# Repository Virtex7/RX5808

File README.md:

# RX5808
FPV Empfänger mit OSD auf OLED, Diversitysupport und vielem mehr.

Software basierend auf dem Projekt von Marko Hoepken
https://code.google.com/p/rx5808-pro/wiki/Overview

sowie inzwischen dem Code des rx5808-pro-diversity von hier:
https://github.com/sheaivey/rx5808-pro-diversity

Es wurden diese Platinen entworfen, um einen vielseitigen FPV-Empfänger bauen zu können

Diese Doku beschränkt sich auf die Hardware, weil die Software schon bei *sheaivey* sehr schön dokumentiert ist.

## Hinweise zur Hardware

Der Hauptgrund für den Bau dieses Moduls ist, dass ich gern ein Modul für die lokale FPV- und Modellbaugruppe designen wollte, das nicht nur die üblichen Funktionen wie freie Kanalwahl, Bandscanner für die Kanalbelegung und übersichtliche Anzeige der Daten hat, sondern auch Diversität unterstützt und allgemein ein schöneres Design hat, als die üblichen Aufbauten. Auch der Schaltwandler direkt auf dem Board hat für eine Bodenstation oder sogar Verwendung direkt an der VR-Brille klare Vorteile.

Dazu kommt, dass ich noch zusätzlich einen HF-Vorverstärker und einen Kopfhöreranschluss verbauen wollte, damit dem Piloten mehr Optionen offen bleiben und das Modul einen Mehrwert gegenüber anderen käuflichen Modulen hat.

Der HF-Verstärker ist auf das 5,8GHz-Band ausgelegt und hat ein Sperrfilter für Signale im 2,4GHz-Band, was im Modellbau heutzutage die Fernsteuerung darstellt. Diese Signale können sonst den Videoempfänger stören und zu Bildstörungen oder sogar dem Totalausfall des Bildes führen, was für die FPV-Piloten fatal ist.

Achtung: HF-Verstärker und Tonausgabe stehen nur bei Verwendung des optionalen Diversity-Moduls zur Verfügung! Es wird auch klar empfohlen, an das Diversity-Erweiterungsmodul keine Richtantennen anzuschließen, wenn der Copter mit einem Funkmodul mit über 25mW Ausgangsleistung und/oder einer Richtantenne ausgestattet ist. Solche Antennen gehören erst mal das Haupt-Empfangsmodul, weil sonst die Gefahr besteht, den Videoempfänger zu überlasten und damit das Videobild zu stören.

Das Diversity-Modul wird automatisch erkannt und dann auch im Menü angezeigt. Es muss keine Änderung an der Software vorgenommen werden. Im Diversity-Modus zeigt eine grüne LED an, welches Modul gerade das Videosignal an den Ausgang liefert. Die Umschaltung zwischen den Empfängern erfolgt für das Videobild unsichtbar.

Schließlich lässt sich noch ein kompatibler Videosender durch eine IR-Schnittstelle auf den gewünschten Kanal einstellen, die dazu nötige IR-Sendediode D5 liegt an einer Platinenecke direkt neben der SMA-Buchse.

## Aufbau
Bestellnummern werden nur bei Bauteilen angegeben, die nicht als "Standardbauteil, also wie ein normaler Kondensator oder Widerstand aus der E12-Reihe, bezeichnet werden können. Leider reicht es nicht aus, ausschließlich bei Digikey zu bestellen, da hier einzelne Teile nicht verfügbar sind. Es gibt in Deutschland keinen Distributor, der alle benötigten Teile liefern kann.

### Bill of Material
| Anzahl | Bauteilname | Gehäuseform | Referenz(en) auf der Platine | Digikeynummer |
| ------ | ----------- | ----------- | ---------------------------- | ------------- |
|

### Platinenlayouts und Löten
Die Platine sind mit KiCAD, einer Version >> 4.0 erstellt und müssen auch damit exportiert werden. Generelle Tips dazu kann ich nicht geben, da es viel zu ausführlich werden würde. Ich empfehle jedoch nicht, für einen Nachbau die Daten direkt zu verwenden, die im Gerber-Verzeichnis sind, sondern stets selbst Fertigungsdaten zu exportieren.

Durch die vielen SMD-Bauteile und vor allem das HF-Filter auf der Diversityplatine bietet sich Reflowlöten klar an. Die Lötpaste kann mittels Dispenser oder auch durch Rakeln aufgebracht werden, wobei ein besonderes Augenmerk auf den kleinen Bauteilen **TPS62160** und **LP38798** gelegt werden sollte. Diese haben ein recht feines Pinraster und kleine Pads, was leicht dazu führen kann, dass die falsche Menge Lötpaste aufgetragen wird.

Von der Reihenfolge her sollte man zuerst die kleinen, meist passiven, Bauelemente auflöten und dann mit den ICs und ggf. Steckern weitermachen. So stehen sich die Bauteile nicht beim Bestücken gegenseitig im Weg herum. Achtung! vor dem Programmieren des Bootloaders **DARF** das OLED noch **NICHT** eingelötet sein, weil man sonst nicht mehr an den Atmel herankäme.

### Test
Bevor das Modul programmiert werden kann, muss es getestet werden. Es geht hier ausschließlich darum, ob der Schaltwandler die richtige Ausgangsspannung liefert. Achtung: nur wenn R21 gesetzt ist, kann der Schaltwandler korrekt arbeiten. Ansonsten gibt er eine leicht zu hohe Spannung aus, weil die Ausgangslast zu gering ist.

Achtung bei der Montage des Kabels zwischen Hauptmodul und Diversityplatine! Die Verpolschutznasen der Micromatchstecker brechen leicht ab und die Diversityplatine ist nicht explizit verpolgeschützt. Daher vor Einschalten der Stromversorgung auf jeden Fall auf korrekte Verkabelung kontrollieren. Beim Verpolen wird zwar die 5V-Versorgung des Moduls auf einen absichtlich nicht verwendeten Pin gelegt, aber durch die Steuersignale könnte dennoch ein Latch-Up-Effekt auftreten.

Die Eingangsspannung wird an den JST-XH-Stecker mit vier Pins angeschlossen, so lange keine Betriebsspannung in den Videoausgang eingespeist wird, ist das Modul verpol- und Überspannungsgeschützt. Sinnvollerweise sollte die Stromversorgung an die beiden oberen Pins des Steckers (Modul liegt so auf dem Tisch, dass der Versorgungsstecker *P1* links liegt) Pin 1 des Steckers ist Power-Masse und Pin 2 Stromversorgung. Für den Test wird hier eine Spannung von 6V eingespeist, weil diese den Mikrocontroller nicht schädigt, wenn der Schaltwandler noch nicht funktioniert, aber eigendlich schon auf 5,0V heruntergeregelt werden sollte. Die Ausgangsspannung kann über den Kondensator C10 leicht gemessen werden; wenn sie passt, also im Breich 4,9 bis 5,1V liegt und sich auch bei Variation der Eingangsspannung nicht ändert, darf die Eingangsspannung auf bis zu 15V angehoben werden. Die Stromaufnahme des Moduls muss hier ohne Empfängermodul etwa bei 10mA liegen. Deutlich höhere Stromaufnahme deutet fast immer auf einen Lötfehler hin.

## Inbetriebnahme
Zuerst muss der Bootloader geflasht werden. Dazu ein ISP-Programmiergerät an den Atmel (ATMEGA328P) anschließen und die Arduino/Genduino-IDE starten. Als Board wird der *Arduino Nano* ausgewählt, der Prozessor ist ein *atmega328* Wenn der Programmiervorgang erfolgreich war, blinkt die eine grüne LED des Hauptboardes mit 1Hz Takt und zeigt so an, dass der Bootloader aufgespielt ist und die Fuses korrekt gesetzt sind.

Jetzt darf das OLED eingelötet werden. **Tipp:** es empfiehlt sich, das OLED mit einem kleinen Stückchen doppelseitigem Klebeband vorne auf den JST-PH-5-Stecker zu kleben, da es so fest ist und nach anlöten nicht mehr verrutschen kann.

### Programmieren der Software

Die Software aus dem Submodul *rx5808-pro-diversity* wird in der Arduino-IDE geöffnet. IDE-Version ab 1.6.6 habe ich getestet, es sollten aber auch frühere Versionen funktionieren. Näheres dazu findet man auch in der Doku beim Entwickler der Software.

**Tipp:** in der Datei *settings.h* lässt sich ein CallSign mit bis zu 10 Zeichen, also z.B. der Name des Piloten, einstellen. Es ist weitaus angenehmer, dieses in der Software am PC einzustellen, als es mit dem kleinen Navigation-Switch direkt am Modul einzugeben.

### Bedienung

Die genaue Bedienung des Geräts ist beim Entwickler der Software zu finden, so viel von mir dazu: Der Navigation-Switch lässt sich nach oben und unten kippen sowie eindrücken. Kippen erzeugt die Funktionen *hoch* und *runter*, Drücken ist die Funktion *Menü* oder im Menü dann *bestätigen*

Es empfiehlt sich, das Modul vor dem ersten richtigen Einsatz zu kalibrieren, der genaue Ablauf steht auch hier in der Softwaredoku.

## Abschließende Hinweise
Das Modul kann eingeschrumpft werden. Dabei bitte auf das OLED aufpassen, die Ecken des Displayglases brechen leicht ab und nehmen dann einen Teil des Folienleiters mit, was das Display zerstört. Ich empfehle, vor dem Einschrumpfen eine kleine Menge Klebstoff unter die Displayecken zu geben, damit diese mechanisch fest sind.
Der Programmierstecker an der unteren Kante des Moduls kann verschlossen werden, er wird für den Betrieb nicht benötigt.

Es ist auch möglich, statt des XH-Steckers für Strom und Videosignal ein Servokabel zu verwenden, auch wenn dies von mir klar nicht empfohlen wird, weil so keine Massetrennung zwischen Signal und Videosignal stattfindet und das Servokabel nicht ziegeschützt ist.
Die Belegung ist so gewählt, dass beim Servokabel Rot und Schwarz die Stromversorgung darstellt und die Signalader das Videosignal führt. Für Tests, oder wenn man gerade keinen XH-Stecker da hat, sicher eine gute Möglichkeit.

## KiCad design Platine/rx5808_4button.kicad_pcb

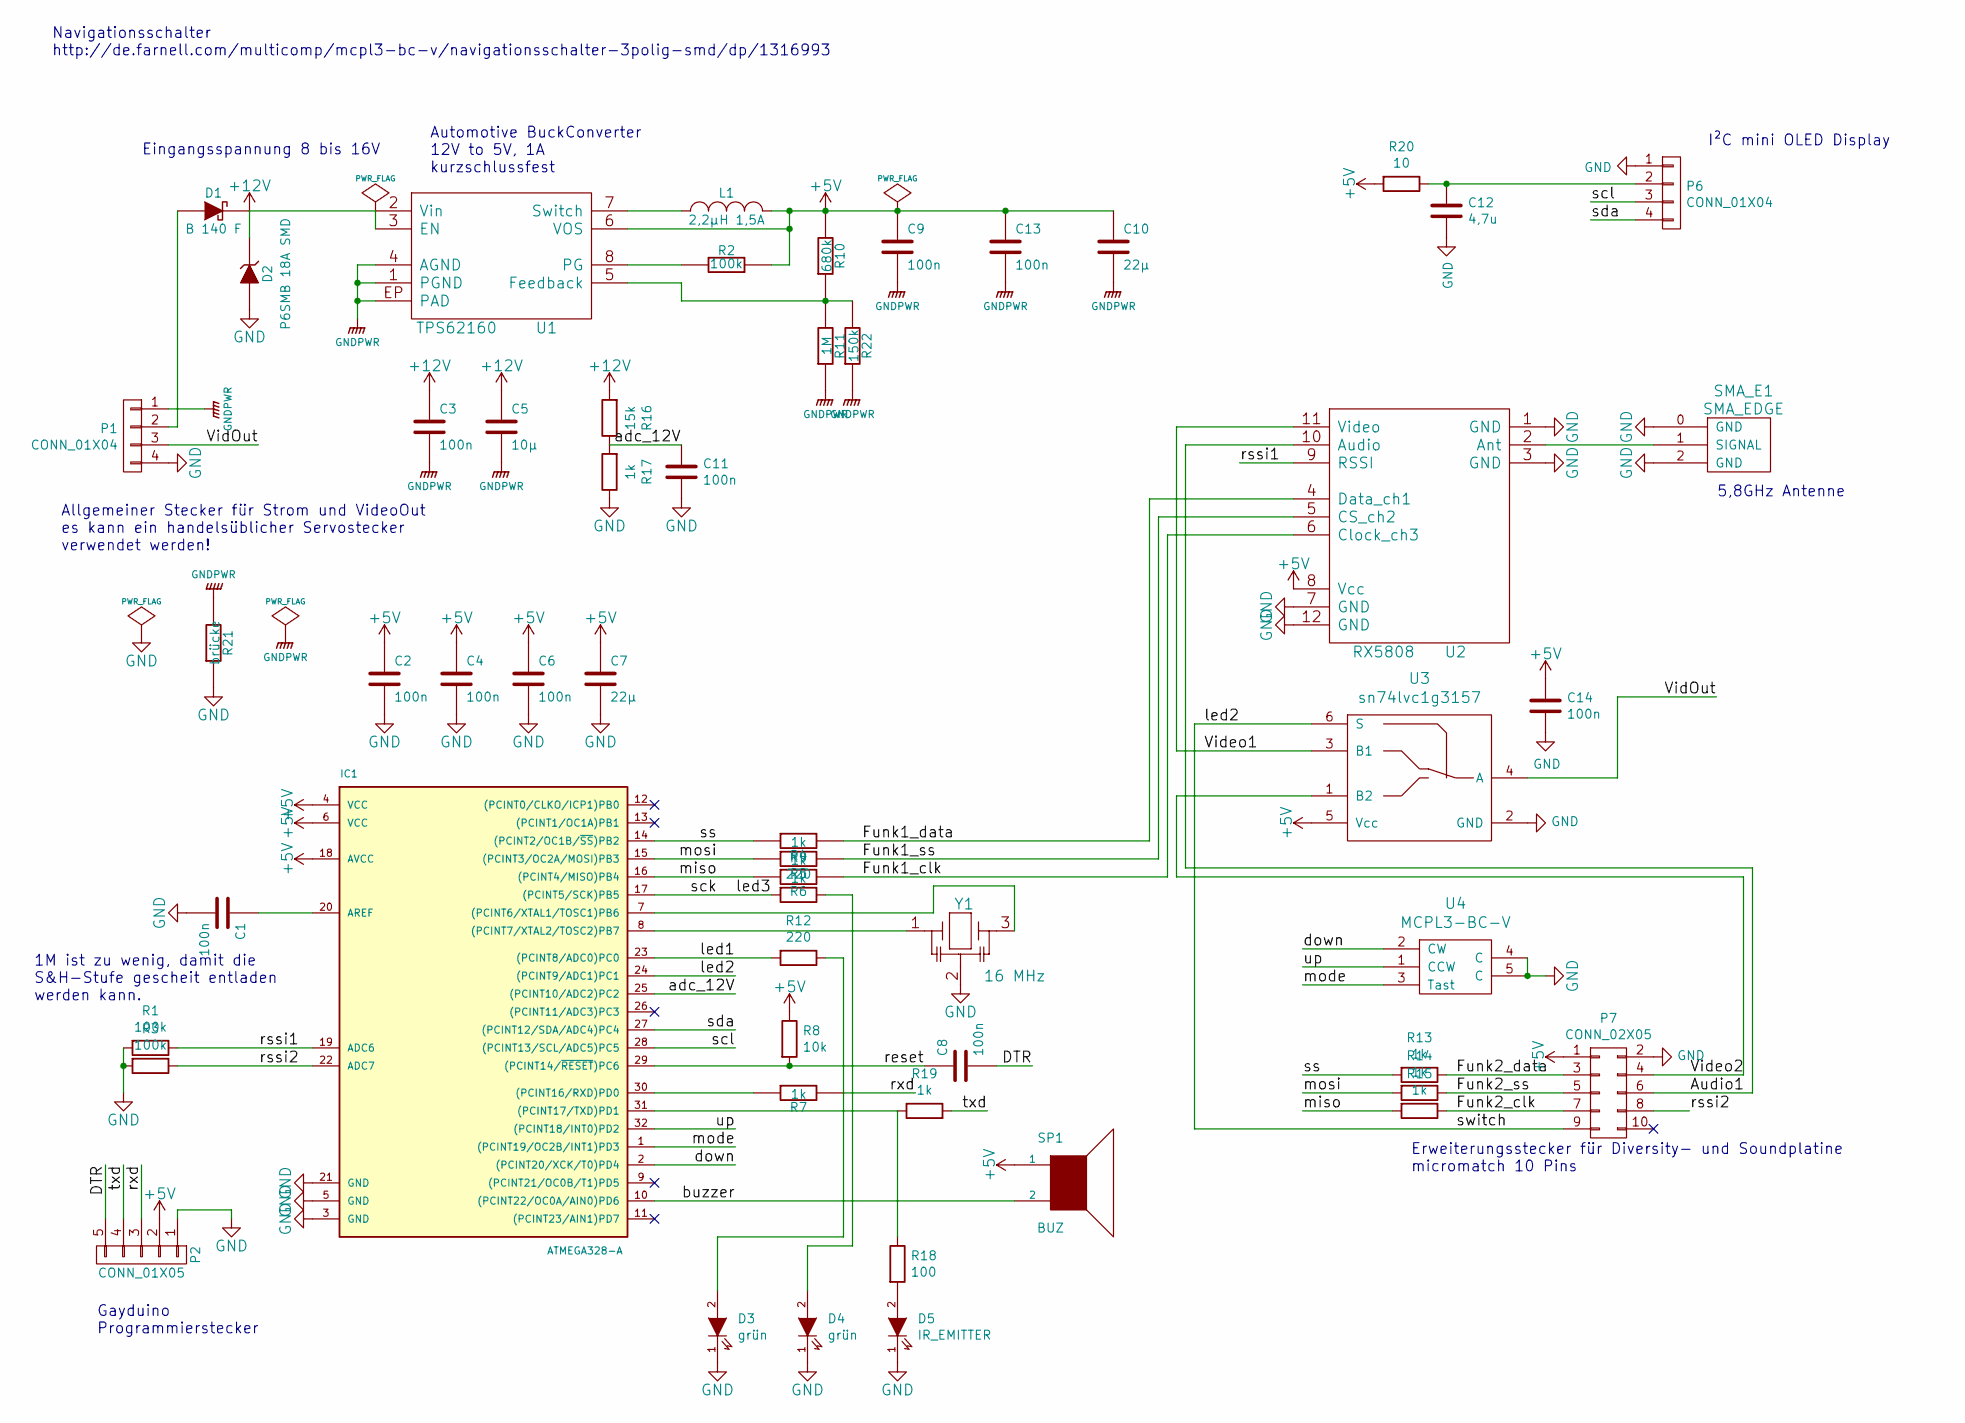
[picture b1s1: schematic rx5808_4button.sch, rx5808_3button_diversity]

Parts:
C1, C2, C3, C4, C6, C8, C9, C11, C13, C14: 100n; C_0603
C5: 10µ; C_1206
C7, C10: 22µ; C_1206
C12: 4,7u; C_0805
D1: B 140 F; SMA_Standard
D2: P6SMB 18A SMD; SMB_Standard
D3, D4: grün; LED_0603
D5: IR_EMITTER; LED_1206
IC1: ATMEGA328-A; TQFP-32_7x7mm_Pitch0.8mm
L1: 2,2µH 1,5A; NR3015; Digikeynummer 587-1648-1-ND
P1: CONN_01X04; JST_XH_S04B-XH-A_04x2.50mm_Angled
P2: CONN_01X05; JST_PH_S5B-PH-SM4-TB_05x2.00mm_Angled
P6: CONN_01X04; Pin_Header_Straight_1x04
P7: CONN_02X05; MICROMATCH-10
R1, R2, R3: 100k; R_0603
R4, R5, R6, R7, R13, R14, R15, R17, R19: 1k; R_0603
R8: 10k; R_0603
R9, R12: 220; R_0603
R10: 680k; R_0603
R11: 1M; R_0603
R16: 15k; R_0603
R18: 100; R_0603
R20: 10; R_0805
R21: brücke; R_0603
R22: 150k; R_0603
SMA_E1: SMA_EDGE; SMA_EDGE_Johnson_142-0701-801
SP1: BUZ; Buzzer_12x9.5RM7.6
U1: TPS62160; DFN-8-1EP_2x2mm_Pitch0.5mm
U2: RX5808
U3: sn74lvc1g3157; SC-70-6
U4: MCPL3-BC-V; MCPL3-AC-V
Y1: 16 MHz; CerOsc_3,2x1,3

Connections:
+5V: C2.1, C4.1, C6.1, C7.1, C9.1, C10.1, C13.1, C14.1, IC1.4 (VCC), IC1.6 (VCC), IC1.18 (AVCC), L1.2, P2.2, P7.1, R2.2, R8.1, R10.1, R20.2, SP1.1, U1.6 (VOS), U2.8 (Vcc), U3.5 (Vcc)
+12V: C3.1, C5.1, D1.2 (K), D2.1 (K), R16.2, U1.2 (Vin), U1.3 (EN)
/Audio1: P7.6, U2.10 (Audio)
/DTR: C8.2, P2.5
/Funk1_clk: R6.1, U2.6 (Clock_ch3)
/Funk1_data: R4.1, U2.4 (Data_ch1)
/Funk1_ss: R5.1, U2.5 (CS_ch2)
/Funk2_clk: P7.7, R15.1
/Funk2_data: P7.3, R13.1
/Funk2_ss: P7.5, R14.1
/VidOut: P1.3, U3.4 (A)
/Video1: U2.11 (Video), U3.3 (B1)
/Video2: P7.4, U3.1 (B2)
/adc_12V: C11.1, IC1.25 ((PCINT10/ADC2)PC2), R16.1, R17.2
/buzzer: IC1.10 ((PCINT22/OC0A/AIN0)PD6), SP1.2
/down: IC1.2 ((PCINT20/XCK/T0)PD4), U4.2 (CW)
/led1: IC1.23 ((PCINT8/ADC0)PC0), R12.2
/led2: IC1.24 ((PCINT9/ADC1)PC1), P7.9, U3.6 (S)
/led3: IC1.17 ((PCINT5/SCK)PB5), R9.2
/miso: IC1.16 ((PCINT4/MISO)PB4), R6.2, R15.2
/mode: IC1.1 ((PCINT19/OC2B/INT1)PD3), U4.3 (Tast)
/mosi: IC1.15 ((PCINT3/OC2A/MOSI)PB3), R5.2, R14.2
/reset: C8.1, IC1.29 ((PCINT14/~RESET~)PC6), R8.2
/rssi1: IC1.19 (ADC6), R1.1, U2.9 (RSSI)
/rssi2: IC1.22 (ADC7), P7.8, R3.1
/rxd: P2.3, R7.1
/scl: IC1.28 ((PCINT13/SCL/ADC5)PC5), P6.3
/sda: IC1.27 ((PCINT12/SDA/ADC4)PC4), P6.4
/ss: IC1.14 ((PCINT2/OC1B/~SS~)PB2), R4.2, R13.2
/txd: P2.4, R19.2
/up: IC1.32 ((PCINT18/INT0)PD2), U4.1 (CCW)
GND: C1.2, C2.2, C4.2, C6.2, C7.2, C11.2, C12.2, C14.2, D2.2 (A), D3.1 (K), D4.1 (K), D5.1 (K), IC1.3 (GND), IC1.5 (GND), IC1.21 (GND), P1.4, P2.1, P6.1, P7.2, R1.2, R3.2, R17.1, R21.2, SMA_E1.0 (GND), SMA_E1.2 (GND), U2.1 (GND), U2.3 (GND), U2.7 (GND), U2.12 (GND), U3.2 (GND), U4.4 (C), U4.5 (C), Y1.2
GNDPWR: C3.2, C5.2, C9.2, C10.2, C13.2, P1.1, R11.2, R21.1, R22.2, U1.1 (PGND), U1.4 (AGND), U1.EP (PAD)
unnamed: C1.1, IC1.20 (AREF)
unnamed: C12.1, P6.2, R20.1
unnamed: D1.1 (A), P1.2
unnamed: D3.2 (A), R12.1
unnamed: D4.2 (A), R9.1
unnamed: D5.2 (A), R18.2
unnamed: IC1.7 ((PCINT6/XTAL1/TOSC1)PB6), Y1.3
unnamed: IC1.8 ((PCINT7/XTAL2/TOSC2)PB7), Y1.1
unnamed: IC1.30 ((PCINT16/RXD)PD0), R7.2
unnamed: IC1.31 ((PCINT17/TXD)PD1), R18.1, R19.1
unnamed: L1.1, U1.7 (Switch)
unnamed: R2.1, U1.8 (PG)
unnamed: R10.2, R11.1, R22.1, U1.5 (Feedback)
unnamed: SMA_E1.1 (SIGNAL), U2.2 (Ant)

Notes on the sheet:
Gayduino Programmierstecker
5,8GHz Antenne
Eingangsspannung 8 bis 16V
Automotive BuckConverter 12V to 5V, 1A kurzschlussfest
I²C mini OLED Display
Erweiterungsstecker für Diversity- und Soundplatine micromatch 10 Pins
Navigationsschalter http://de.farnell.com/multicomp/mcpl3-bc-v/navigationsschalter-3polig-smd/dp/1316993
1M ist zu wenig, damit die S&H-Stufe gescheit entladen werden kann.
Allgemeiner Stecker für Strom und VideoOut es kann ein handelsüblicher Servostecker verwendet werden!

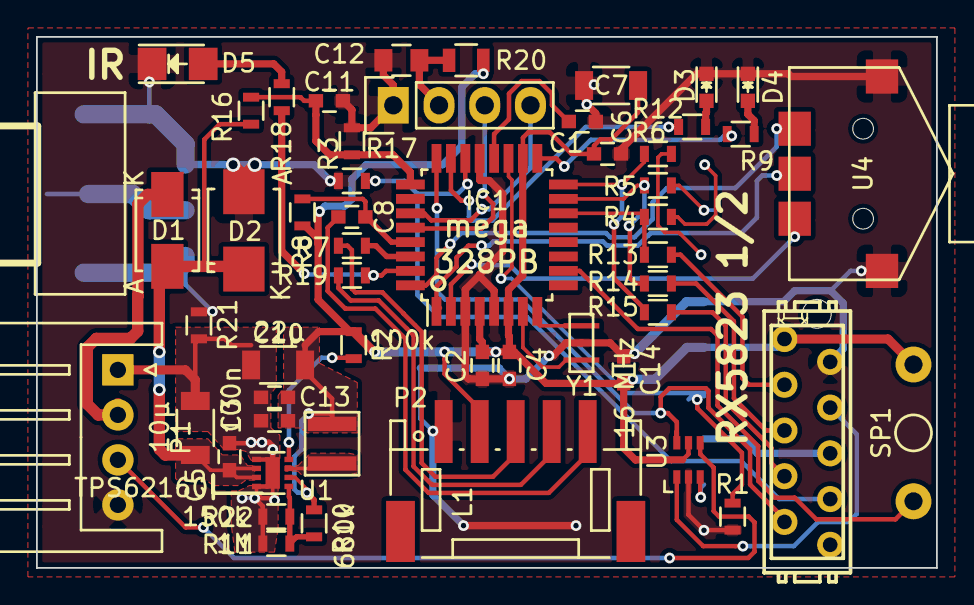
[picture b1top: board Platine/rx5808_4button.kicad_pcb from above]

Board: 2 copper layers, 50.0 x 29.5 mm, 54 parts (1 on the bottom side), 47 nets.

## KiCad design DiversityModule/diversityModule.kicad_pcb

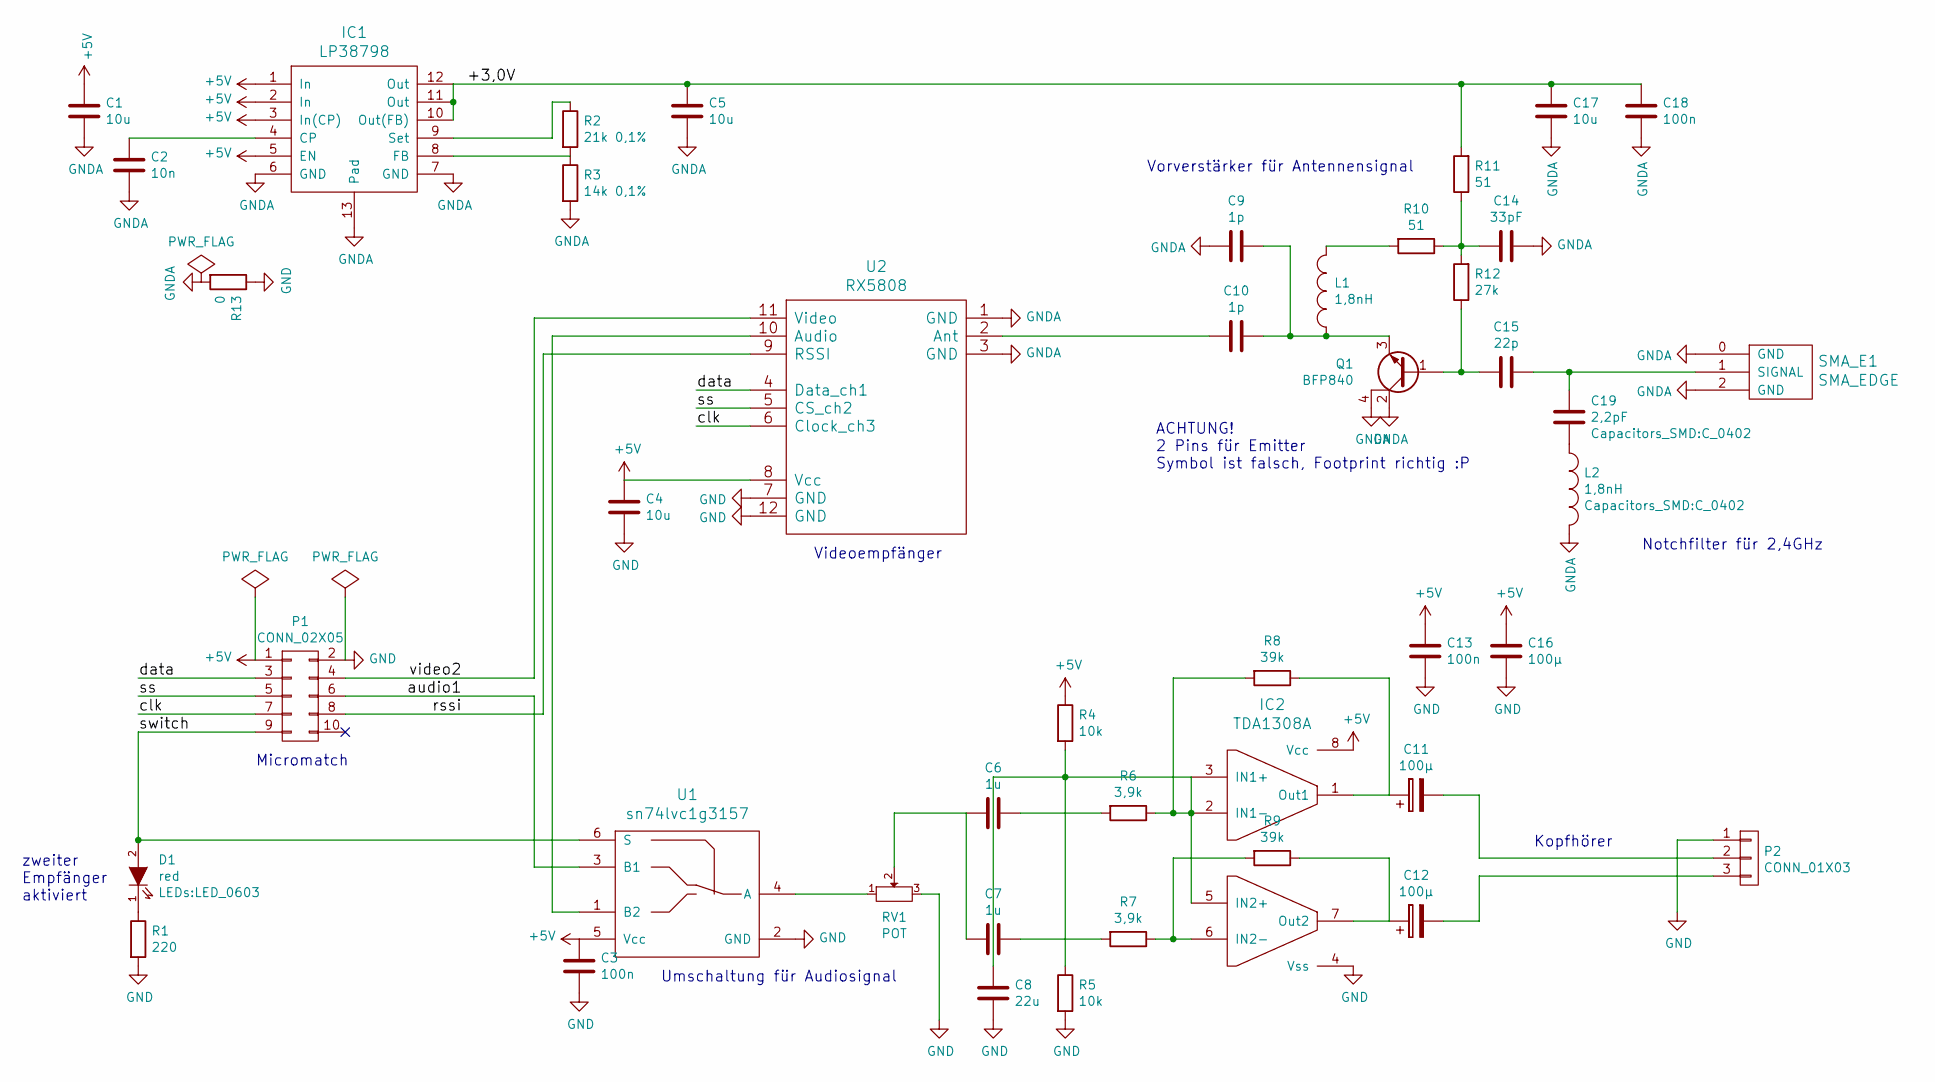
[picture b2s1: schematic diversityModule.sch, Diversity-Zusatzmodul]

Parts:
C1, C4, C5, C17: 10u; C_0805
C2: 10n; C_0603
C3, C13, C18: 100n; C_0603
C6, C7: 1u; C_0603
C8: 22u; C_0805
C9, C10: 1p; C_0603
C11, C12, C16: 100µ; C_1210
C14: 33pF; C_0603
C15: 22p; C_0603
C19: 2,2pF; C_0402
D1: red; LED_0603
IC1: LP38798; DFN-12-1EP_4x4mm_Pitch0.5mm
IC2: TDA1308A; SOIC-8_3.9x4.9mm_Pitch1.27mm
L1: 1,8nH; R_0402
L2: 1,8nH; C_0402
P1: CONN_02X05; MICROMATCH-10
P2: CONN_01X03; LUM1503-03
Q1: BFP840; SOT-143
R1: 220; R_0603
R2: 21k 0,1%; R_0805; Digikeynummer YAG1828CT-ND
R3: 14k 0,1%; R_0805; Digikeynummer YAG1783CT-ND
R4, R5: 10k; R_0603
R6, R7: 3,9k; R_0603
R8, R9: 39k; R_0603
R10, R11: 51; R_0402
R12: 27k; R_0402
R13: 0; R_0805; Digikeynummer YAG1783CT-ND
RV1: POT; Poti-SMD-Model-23A
SMA_E1: SMA_EDGE; SMA_EDGE_Johnson_142-0701-801
U1: sn74lvc1g3157; SC-70-6
U2: RX5808

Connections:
+5V: C1.1, C3.1, C4.1, C13.1, C16.1, IC1.1 (In), IC1.2 (In), IC1.3 (In(CP)), IC1.5 (EN), IC2.8 (Vcc), P1.1, R4.1, U1.5 (Vcc), U2.8 (Vcc)
/+3,0V: C5.1, C17.1, C18.1, IC1.10 (Out(FB)), IC1.11 (Out), IC1.12 (Out), R11.2
/audio1: P1.6, U1.3 (B1)
/clk: P1.7, U2.6 (Clock_ch3)
/data: P1.3, U2.4 (Data_ch1)
/rssi: P1.8, U2.9 (RSSI)
/ss: P1.5, U2.5 (CS_ch2)
/switch: D1.2 (A), P1.9, U1.6 (S)
/video2: P1.4, U2.11 (Video)
GND: C3.2, C4.2, C8.2, C13.2, C16.2, IC2.4 (Vss), P1.2, P2.1, R1.2, R5.2, R13.1, RV1.3, U1.2 (GND), U2.7 (GND), U2.12 (GND)
GNDA: C1.2, C2.2, C5.2, C9.2, C14.1, C17.2, C18.2, IC1.6 (GND), IC1.7 (GND), IC1.13 (Pad), L2.2, Q1.2 (C), Q1.4 (C), R3.2, R13.2, SMA_E1.0 (GND), SMA_E1.2 (GND), U2.1 (GND), U2.3 (GND)
unnamed: C2.1, IC1.4 (CP)
unnamed: C6.1, R6.2
unnamed: C6.2, C7.2, RV1.2
unnamed: C7.1, R7.2
unnamed: C8.1, IC2.2 (IN1-), IC2.3 (IN1+), IC2.5 (IN2+), R4.2, R5.1, R6.1, R8.2
unnamed: C9.1, C10.1, L1.2, Q1.3 (E)
unnamed: C10.2, U2.2 (Ant)
unnamed: C11.1, IC2.1 (Out1), R8.1
unnamed: C11.2, P2.2
unnamed: C12.1, IC2.7 (Out2), R9.1
unnamed: C12.2, P2.3
unnamed: C14.2, R10.1, R11.1, R12.2
unnamed: C15.1, C19.1, SMA_E1.1 (SIGNAL)
unnamed: C15.2, Q1.1 (B), R12.1
unnamed: C19.2, L2.1
unnamed: D1.1 (K), R1.1
unnamed: IC1.8 (FB), R2.2, R3.1
unnamed: IC1.9 (Set), R2.1
unnamed: IC2.6 (IN2-), R7.1, R9.2
unnamed: L1.1, R10.2
unnamed: RV1.1, U1.4 (A)
unnamed: U1.1 (B2), U2.10 (Audio)

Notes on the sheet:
Umschaltung für Audiosignal
Videoempfänger
zweiter Empfänger aktiviert
Micromatch
Kopfhörer
Vorverstärker für Antennensignal
ACHTUNG! 2 Pins für Emitter Symbol ist falsch, Footprint richtig :P
Notchfilter für 2,4GHz

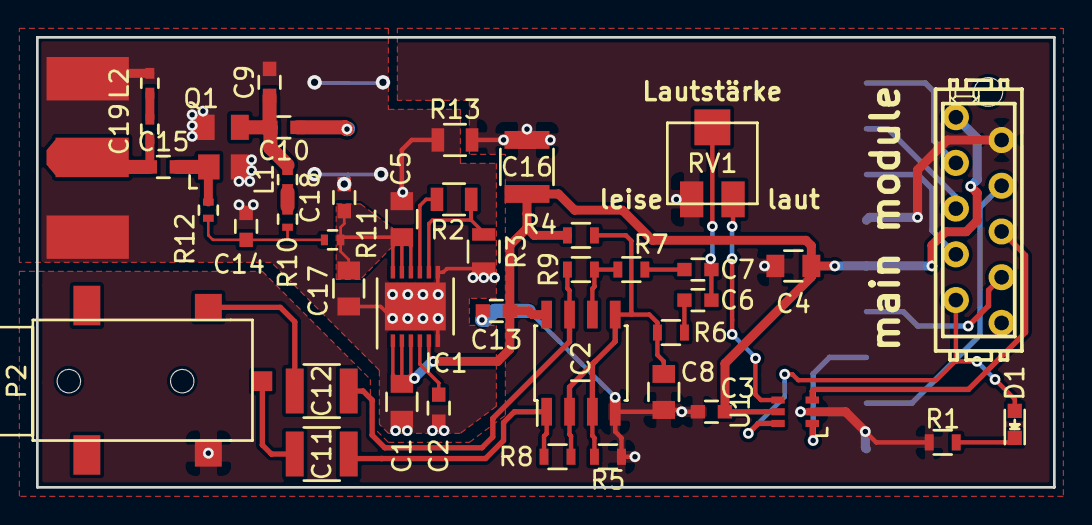
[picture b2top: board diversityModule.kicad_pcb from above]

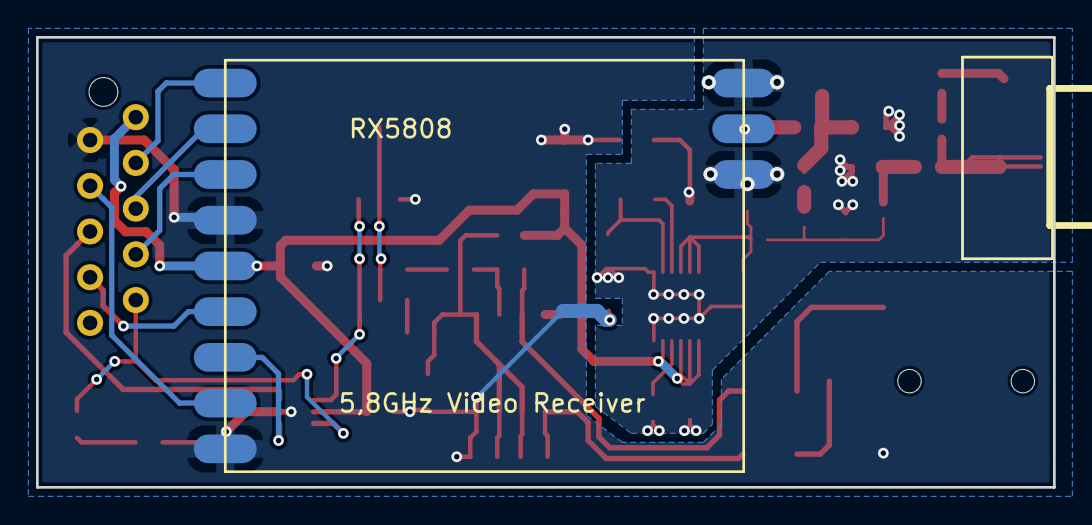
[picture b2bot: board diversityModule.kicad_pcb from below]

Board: 2 copper layers, 56.5 x 25.0 mm, 44 parts (2 on the bottom side), 33 nets.

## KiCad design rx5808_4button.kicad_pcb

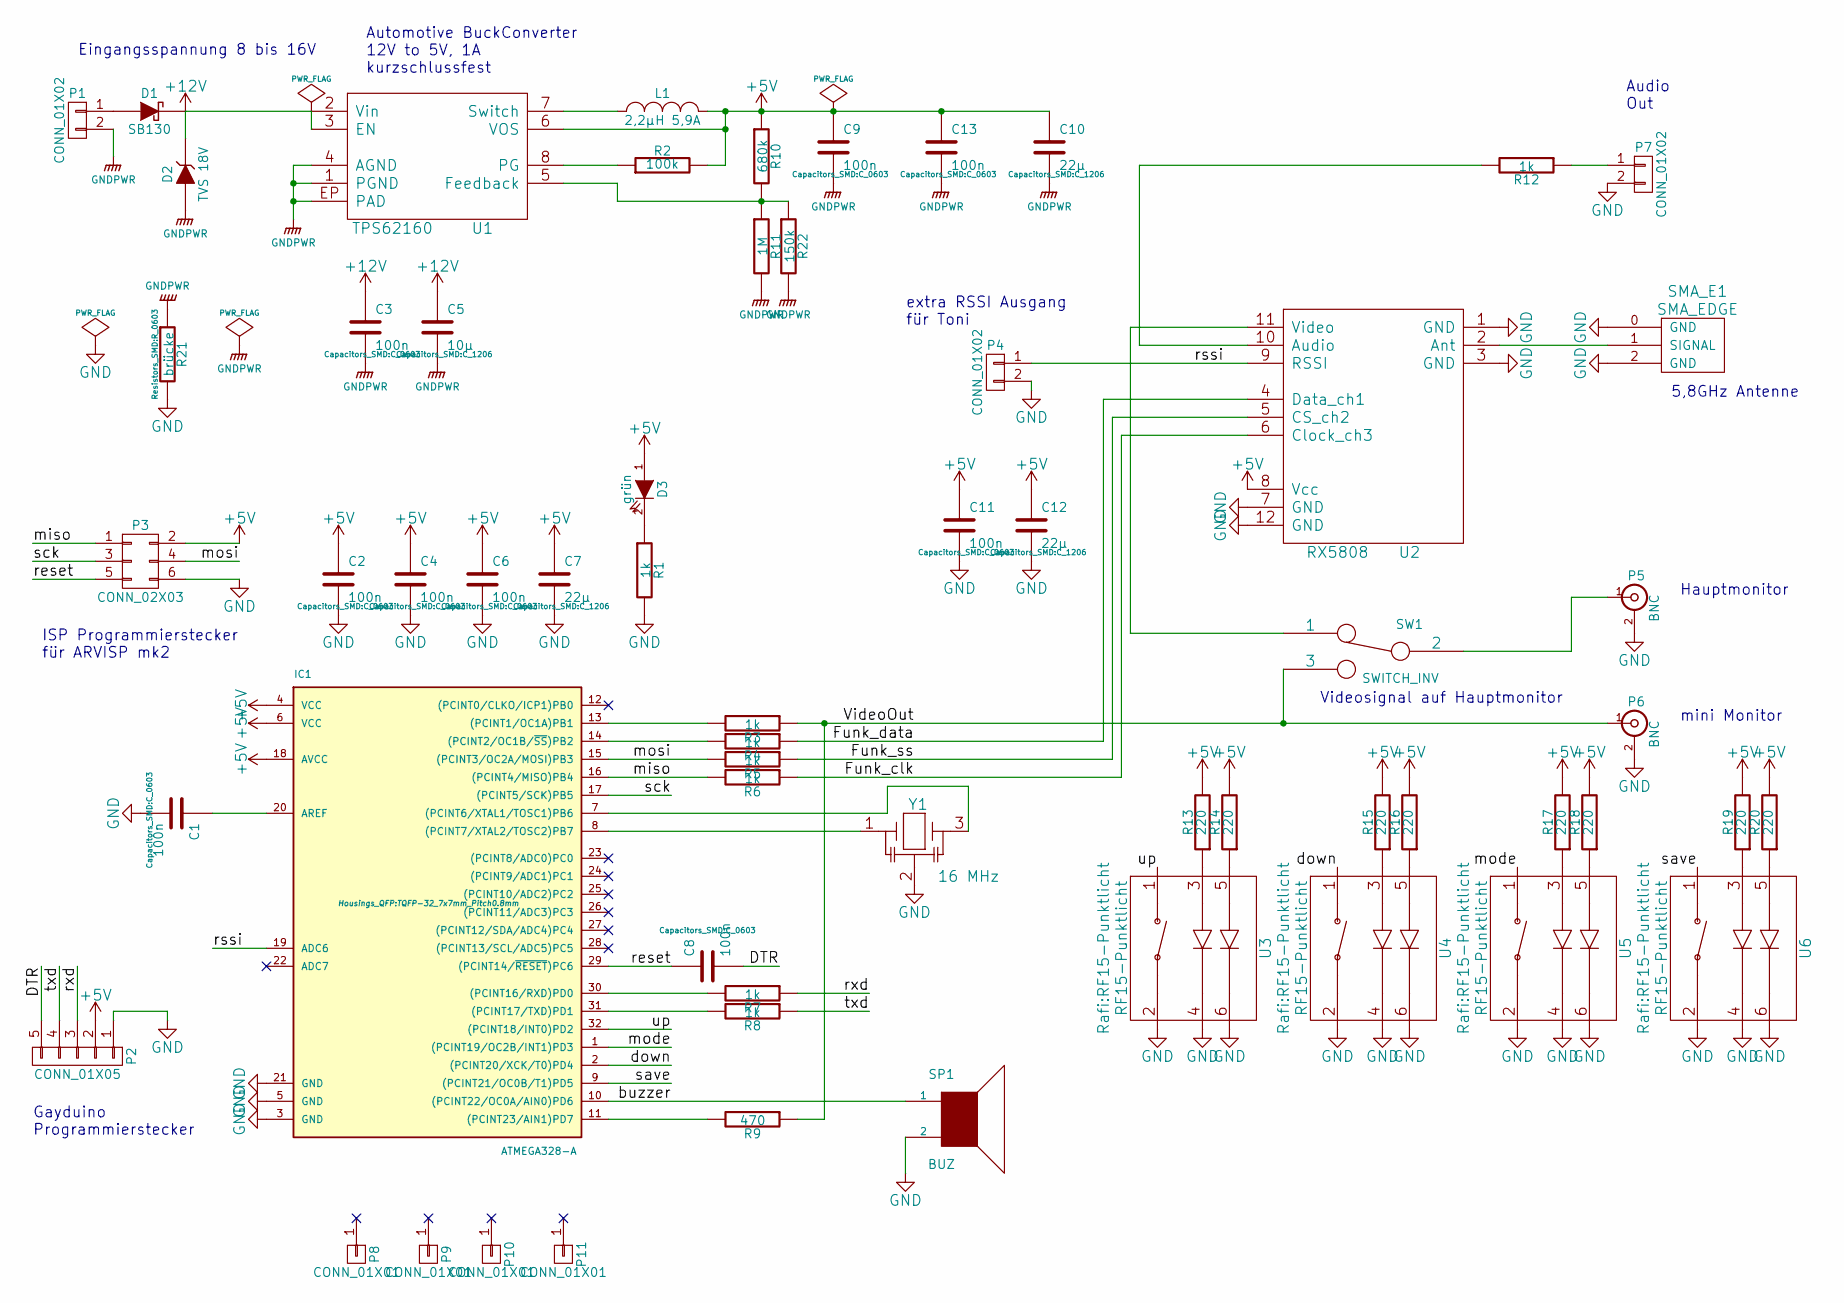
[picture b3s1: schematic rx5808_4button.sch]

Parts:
C1, C2, C3, C4, C6, C8, C9, C11, C13: 100n; C_0603
C5: 10µ; C_1206
C7, C10, C12: 22µ; C_1206
D1: SB130; Diode-SMA_Standard
D2: TVS 18V; Diode-SMB_Standard
D3: grün; LED-0603
IC1: ATMEGA328-A; TQFP-32_7x7mm_Pitch0.8mm
L1: 2,2µH 5,9A; VLF4012A
P1: CONN_01X02; Socket_MOLEX-KK-RM2-54mm_Lock_2pin_straight
P2: CONN_01X05; Pin_Header_Straight_1x05
P3: CONN_02X03; Pin_Header_Straight_2x03
P4, P7: CONN_01X02; Pin_Header_Straight_1x02
P5, P6: BNC; Cinch_angled_mono
P8, P9, P10, P11: CONN_01X01; MountingHole_3-5mm
R1, R3, R4, R5, R6, R7, R8, R12: 1k; R_0603
R2: 100k; R_0603
R9: 470; R_0603
R10: 680k; R_0603
R11: 1M; R_0603
R13, R14, R15, R16, R17, R18, R19, R20: 220; R_0603
R21: brücke; R_0603
R22: 150k; R_0603
SMA_E1: SMA_EDGE
SP1: BUZ; Buzzer_12x9.5RM7.6
SW1: SWITCH_INV; 2543xN
U1: TPS62160; DFN-8-1EP_2x2mm_Pitch0.5mm
U2: RX5808
U3, U4, U5, U6: RF15-Punktlicht
Y1: 16 MHz; CerOsc_3,2x1,3

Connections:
+5V: C2.1, C4.1, C6.1, C7.1, C9.1, C10.1, C11.1, C12.1, C13.1, D3.1 (A), IC1.4 (VCC), IC1.6 (VCC), IC1.18 (AVCC), L1.2, P2.2, P3.2, R2.2, R10.1, R13.2, R14.2, R15.2, R16.2, R17.2, R18.2, R19.2, R20.2, U1.6 (VOS), U2.8 (Vcc)
+12V: C3.1, C5.1, D1.2 (K), D2.2 (K), U1.2 (Vin), U1.3 (EN)
/DTR: C8.2, P2.5
/Funk_clk: R6.1, U2.6 (Clock_ch3)
/Funk_data: R4.1, U2.4 (Data_ch1)
/Funk_ss: R5.1, U2.5 (CS_ch2)
/VideoOut: P6.1 (In), R3.1, R9.1, SW1.3
/buzzer: IC1.10 ((PCINT22/OC0A/AIN0)PD6), SP1.1
/down: IC1.2 ((PCINT20/XCK/T0)PD4), U4.1
/miso: IC1.16 ((PCINT4/MISO)PB4), P3.1, R6.2
/mode: IC1.1 ((PCINT19/OC2B/INT1)PD3), U5.1
/mosi: IC1.15 ((PCINT3/OC2A/MOSI)PB3), P3.4, R5.2
/reset: C8.1, IC1.29 ((PCINT14/~RESET~)PC6), P3.5
/rssi: IC1.19 (ADC6), P4.1, U2.9 (RSSI)
/rxd: P2.3, R7.1
/save: IC1.9 ((PCINT21/OC0B/T1)PD5), U6.1
/sck: IC1.17 ((PCINT5/SCK)PB5), P3.3
/txd: P2.4, R8.1
/up: IC1.32 ((PCINT18/INT0)PD2), U3.1
GND: C1.2, C2.2, C4.2, C6.2, C7.2, C11.2, C12.2, IC1.3 (GND), IC1.5 (GND), IC1.21 (GND), P2.1, P3.6, P4.2, P5.2 (Ext), P6.2 (Ext), P7.2, R1.2, R21.2, SMA_E1.0 (GND), SMA_E1.2 (GND), SP1.2, U2.1 (GND), U2.3 (GND), U2.7 (GND), U2.12 (GND), U3.2, U3.4, U3.6, U4.2, U4.4, U4.6, U5.2, U5.4, U5.6, U6.2, U6.4, U6.6, Y1.2
GNDPWR: C3.2, C5.2, C9.2, C10.2, C13.2, D2.1 (A), P1.2, R11.2, R21.1, R22.2, U1.1 (PGND), U1.4 (AGND), U1.EP (PAD)
unnamed: C1.1, IC1.20 (AREF)
unnamed: D1.1 (A), P1.1
unnamed: D3.2 (K), R1.1
unnamed: IC1.7 ((PCINT6/XTAL1/TOSC1)PB6), Y1.3
unnamed: IC1.8 ((PCINT7/XTAL2/TOSC2)PB7), Y1.1
unnamed: IC1.11 ((PCINT23/AIN1)PD7), R9.2
unnamed: IC1.13 ((PCINT1/OC1A)PB1), R3.2
unnamed: IC1.14 ((PCINT2/OC1B/~SS~)PB2), R4.2
unnamed: IC1.30 ((PCINT16/RXD)PD0), R7.2
unnamed: IC1.31 ((PCINT17/TXD)PD1), R8.2
unnamed: L1.1, U1.7 (Switch)
unnamed: P5.1 (In), SW1.2
unnamed: P7.1, R12.1
unnamed: R2.1, U1.8 (PG)
unnamed: R10.2, R11.1, R22.1, U1.5 (Feedback)
unnamed: R12.2, U2.10 (Audio)
unnamed: R13.1, U3.3
unnamed: R14.1, U3.5
unnamed: R15.1, U4.3
unnamed: R16.1, U4.5
unnamed: R17.1, U5.3
unnamed: R18.1, U5.5
unnamed: R19.1, U6.3
unnamed: R20.1, U6.5
unnamed: SMA_E1.1 (SIGNAL), U2.2 (Ant)
unnamed: SW1.1, U2.11 (Video)

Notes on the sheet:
ISP Programmierstecker für ARVISP mk2
Gayduino Programmierstecker
Videosignal auf Hauptmonitor
Hauptmonitor
mini Monitor
5,8GHz Antenne
Eingangsspannung 8 bis 16V
Automotive BuckConverter 12V to 5V, 1A kurzschlussfest
Audio Out
extra RSSI Ausgang für Toni

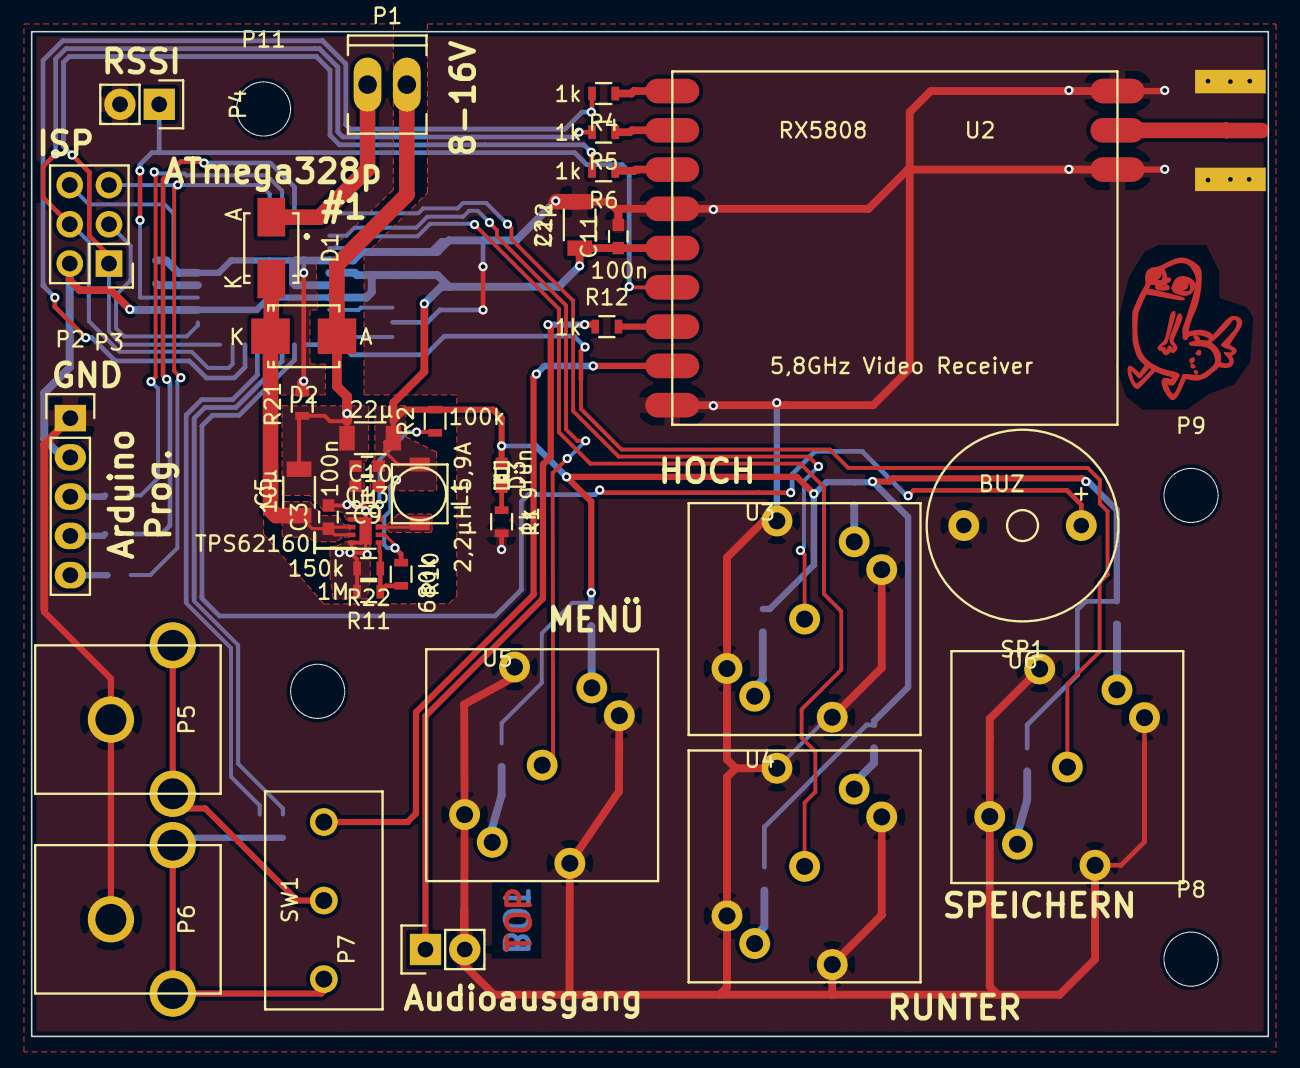
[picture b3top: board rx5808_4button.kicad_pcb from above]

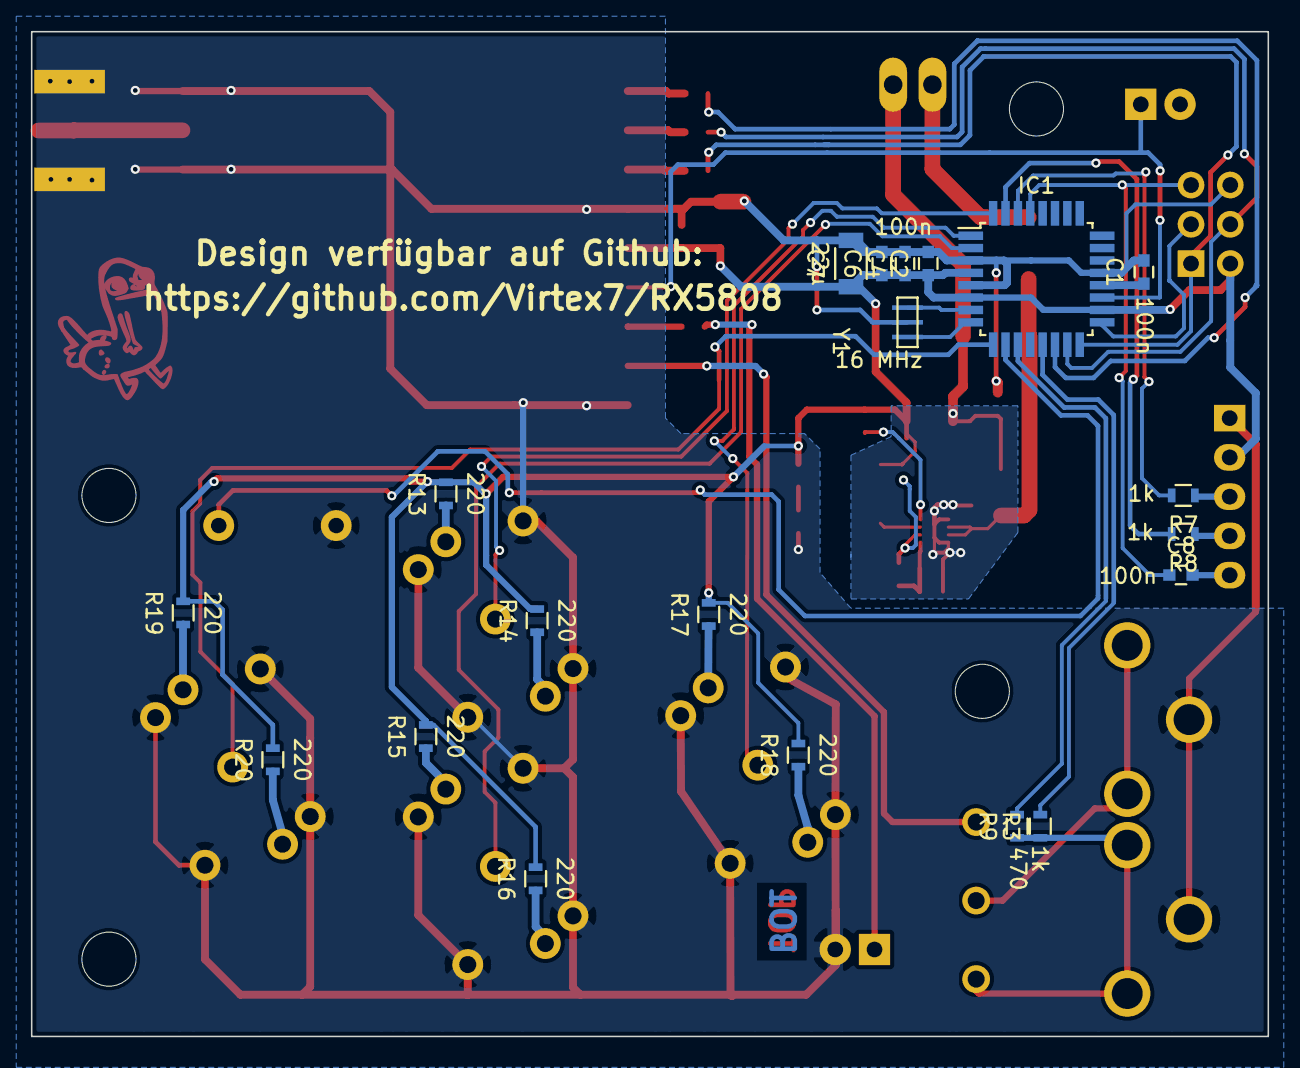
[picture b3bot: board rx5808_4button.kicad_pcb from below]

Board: 2 copper layers, 80.0 x 65.0 mm, 61 parts (20 on the bottom side), 47 nets.

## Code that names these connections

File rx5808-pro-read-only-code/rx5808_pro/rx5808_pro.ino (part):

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#define buttonDown 4
#define buttonSave 5
// Buzzer
#define buzzer 6
// pins for DIP switch
#define dip_ch0 A0
#define dip_ch1 A1
#define dip_ch2 A2
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
uint8_t channel = 0;
uint8_t channelIndex = 0;
uint8_t rssi = 0;
uint8_t rssi_scaled = 0;
uint8_t hight = 0;
uint8_t state = START_STATE;
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    // initialize digital pin 13 LED as an output.
    pinMode(led, OUTPUT); // status pin for TV mode errors
    // buzzer
    pinMode(buzzer, OUTPUT); // Feedback buzzer (active buzzer, not passive piezo)   
    digitalWrite(buzzer, LOW);
    // minimum control pins
    pinMode(buttonSeek, INPUT);
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
uint16_t readRSSI() 
{
    uint16_t rssi = 0;
    for (uint8_t i = 0; i < 10; i++) 
    {
        rssi += analogRead(rssiPin);
    }
    rssi=rssi/10; // average
    // special case for RSSI setup
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        TV.print(1,20, "RAW:             ");
        TV.print(30,20, rssi, DEC);    
    #endif
    rssi = constrain(rssi, rssi_min, rssi_max);    //original 90---250
    rssi=rssi-rssi_min; // set zero point (value 0...160)
    rssi = map(rssi, 0, rssi_max-rssi_min , 1, 100);   // scale from 1..100%
    #ifdef RSSI_DEBUG
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
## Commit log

2015-02-26 inital commit nach Ersetellen des Schaltplanes
2015-02-26 schaltplan weiter und mehr Footprints erstellt
2015-02-27 Footprints für alle Taster und Schalter erstellt, inital commit für Platine
2015-02-27 Layout fertig und Footprint für SMA geaddet.
2015-02-28 andere Spule und neues Layout für den Schaltwandler
2015-02-28 Schaltwandler weiter verbessert
2015-02-28 finale änderungen an Leiterbahnen
2015-03-21 rssi-anschluss für externe RSSI-Anzeige dazugebaut
2015-03-23 Bilder für SPI-Mod der neuen Version des Empfängermoduls
2015-03-24 neue Bilder dazugefügt
2015-03-25 code und TVLIB dem sourcecode geadded, weil die quellen nicht als submodule eingebunden werden können.
2015-03-30 funktionierendes hexfile hinzugefügt
2015-04-02 symbol hinzugefügt
2015-04-04 RCA-Lib angelegt
2015-04-04 dickbutt inserted
2015-04-04 RCA-Lib erstellt
2015-04-04 Layout fertig - cinchbuchsen für Video eingebaut.
2015-04-04 SMA-buchse richtig gestellt
2015-04-04 130k-Ohm durch zwei parallele Widerstände ersetzt, um eine vollständige E12-Kompatibilität gewährleisten zu können
2015-04-04 footprint cinch angepasst (npth löcher gelöscht)
2015-04-04 letzte Änderungen für Fertigung
2015-05-20 mehr zeug in die gitignore und etwas Ordnung gemacht.
2015-05-20 Platinendesigndaten in einen extra ordner verschoben
2015-05-20 readme versehentlich verschoben - fehler beseitigt
2015-05-20 noch eine datei weg...
2015-05-26 das neue Immersion RC RaceBand kommt zum Empfänger dazu!
2015-06-05 IRC Race Band teilweise implementiert
2015-07-10 beep invertiert
2016-03-28 neues diversityprojekt hinzugefügt
2016-04-07 neue LIB für den micromatchstecker
2016-04-07 Footprint für neue spule hinzugefügt
2016-04-07 Platine fertig und exportiert.
2016-04-07 diversity-empfangsmodul schaltplan dazugefügt
2016-04-13 Layout fertig. Überprüfung steht aus.
2016-04-20 BOM für beide platinen des kompletten moduls dazugefügt
2016-04-23 Exports vom neuen Layout
2016-05-07 schaltplan und netzliste für die beiden issues geändert.
2016-05-07 jetzt auch layout geändert. micromatchbuchse und/oder buzzer sollten noch verschoben werden!
2016-05-24 neue appNote für ein 2,4GHz notchfilter
2016-06-07 fuses-datei für den Atmega328PB dazugefügt, Bootloaderstecker auf JST PH geändert, Filterkondensator und Widerstand für OLED hinzugefügt
2016-06-07 RC-Filter für OLED hinzugefügt und eingelayoutet
2016-06-07 Layoutänderungen für videoumschalter (anderes gehäuse)
2016-06-13 Klinkenbuchse ausgetauscht und zur Lib hinzugefügt.
2016-06-13 vergessen, das Layout zu speichern.
2016-07-08 initial commit outline und pinheader platziert
2016-08-30 BOM hinzugefügt
2016-08-31 BOM fertiggestellt und alten Code gelöscht
2016-09-01 alten Code gelöscht und README etwas erweitert.
2016-09-02 Hexfile vom alten Code gelöscht und README-md weitergeschrieben

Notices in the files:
rx5808-pro-read-only-code/rx5808_pro/rx5808_pro.ino:
The MIT License (MIT)
Copyright (c) 2015 Marko Hoepken
